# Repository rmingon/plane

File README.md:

# PLANE  with 3D models and specific hardware control system 

* SG90 servo
* LD-POWER motor 4300KV
* ESC 8A 
* 2-3s battery

### Thingiverse
[LINK](https://www.thingiverse.com/thing:6716661)

### 3d global view

## Hardware

* ESP32 wifi + bluetooth controller
* LORA 868mhz Long range communication with SMA connector
* 4 channels servos control
* XT30 battery connector
* MPU6050 giro and accel mcu
* BMP280 altimeter
* ESC connector

### 3d view

### Pcb view

### Schematic view

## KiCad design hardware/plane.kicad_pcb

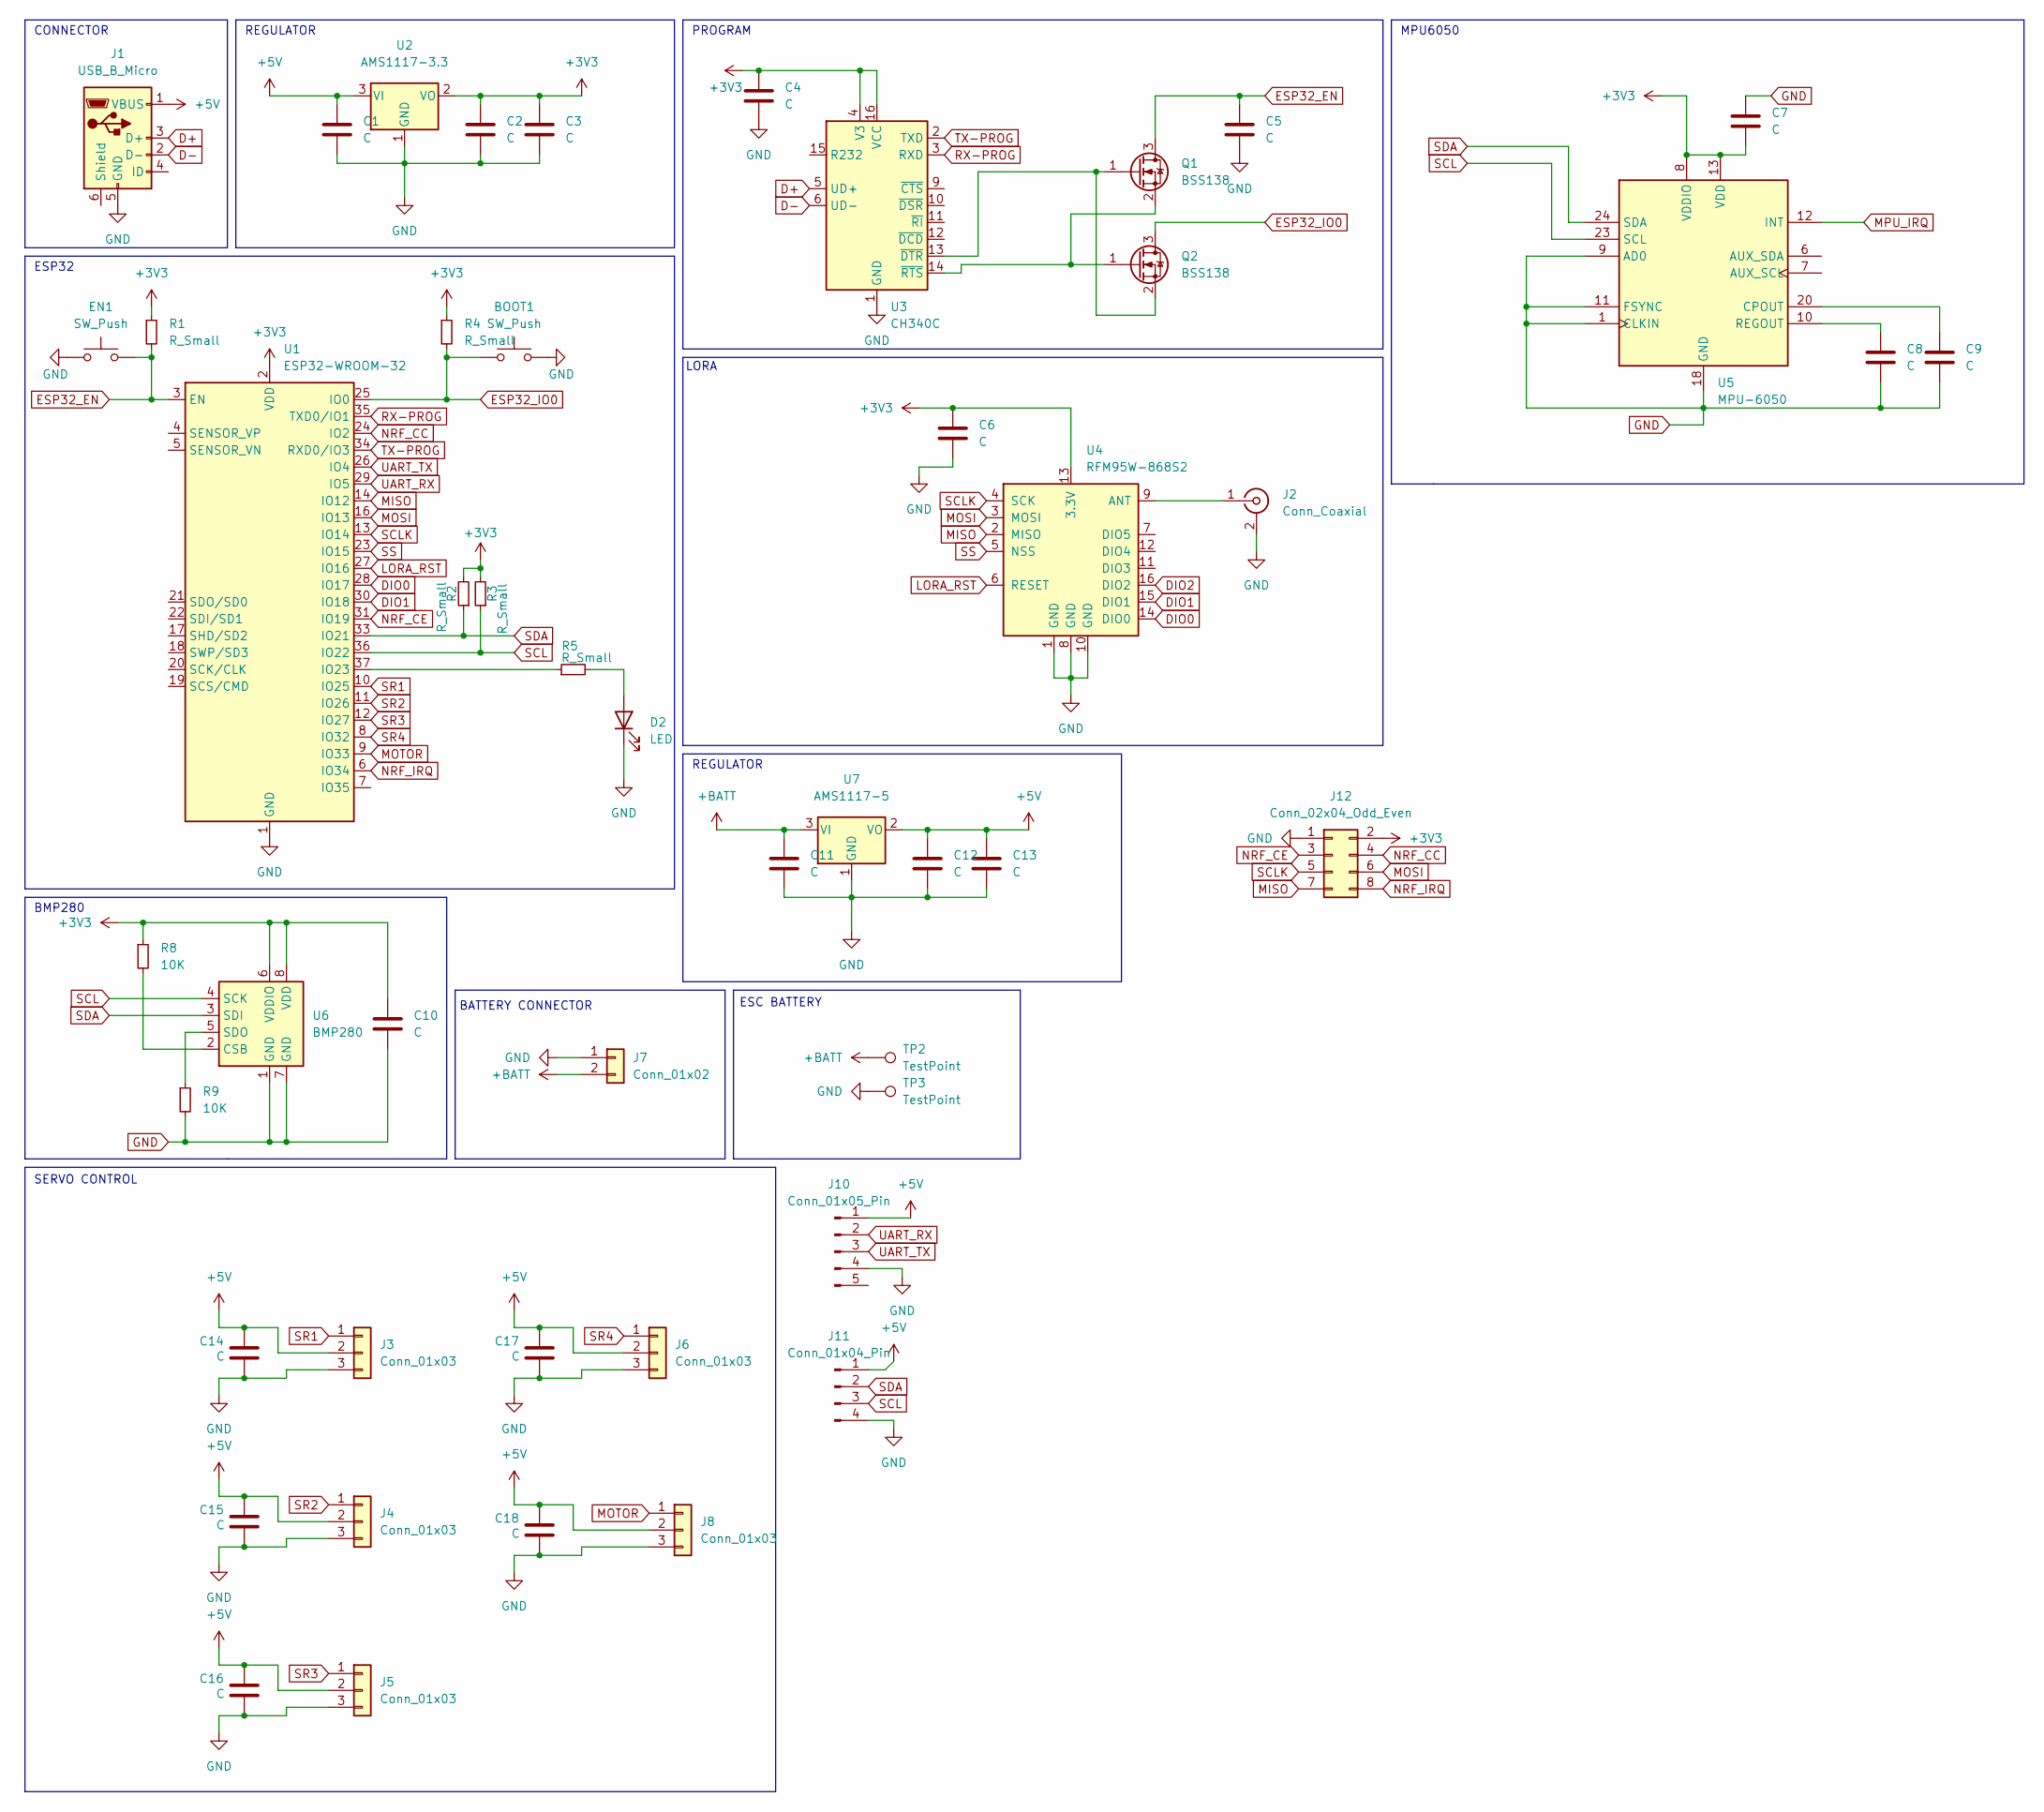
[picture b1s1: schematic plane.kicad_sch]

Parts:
BOOT1: SW_Push; SW_SPST_FSMSM
C1, C2, C3, C4, C5, C6, C7, C8, C9, C10, C11, C12, C13, C14, C15, C16, C17, C18: C; C_0603_1608Metric
D2: LED; LED_0603_1608Metric
EN1: SW_Push; SW_SPST_FSMSM
J1: USB_B_Micro; USB_Micro-B_Amphenol_10118194_Horizontal
J2: Conn_Coaxial; SMA_Samtec_SMA-J-P-H-ST-EM1_EdgeMount
J3, J4, J5, J6, J8: Conn_01x03; PinHeader_1x03_P2.54mm_Vertical
J7: Conn_01x02; AMASS_XT30U-F_1x02_P5.0mm_Vertical
J10: Conn_01x05_Pin; PinHeader_1x05_P2.54mm_Vertical
J11: Conn_01x04_Pin; PinHeader_1x04_P2.54mm_Vertical
J12: Conn_02x04_Odd_Even; PinHeader_2x04_P2.54mm_Vertical
Q1, Q2: BSS138; SOT-23
R1, R2, R3, R4, R5: R_Small; R_0603_1608Metric
R8, R9: 10K; R_0603_1608Metric
TP2, TP3: TestPoint; TestPoint_Pad_2.5x2.5mm
U1: ESP32-WROOM-32
U2: AMS1117-3.3; SOT-223-3_TabPin2
U3: CH340C; SOIC-16_3.9x9.9mm_P1.27mm
U4: RFM95W-868S2; HOPERF_RFM9XW_SMD
U5: MPU-6050; InvenSense_QFN-24_4x4mm_P0.5mm
U6: BMP280; Bosch_LGA-8_2x2.5mm_P0.65mm_ClockwisePinNumbering
U7: AMS1117-5; SOT-223-3_TabPin2

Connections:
+3V3: C2.1, C3.1, C4.1, C6.1, C7.2, C10.1, J12.2, R1.1, R2.2, R3.2, R4.1, R8.1, U1.2 (VDD), U2.2 (VO), U3.4 (V3), U3.16 (VCC), U4.13 (3.3V), U5.8 (VDDIO), U5.13 (VDD), U6.6 (VDDIO), U6.8 (VDD)
+5V: C1.1, C12.1, C13.1, C14.1, C15.1, C16.1, C17.1, C18.1, J1.1 (VBUS), J3.2, J4.2, J5.2, J6.2, J8.2, J10.1, J11.1, U2.3 (VI), U7.2 (VO)
+BATT: C11.1, J7.2, TP2.1, U7.3 (VI)
D+: J1.3 (D+), U3.5 (UD+)
D-: J1.2 (D-), U3.6 (UD-)
DIO0: U1.28 (IO17), U4.14 (DIO0)
DIO1: U1.30 (IO18), U4.15 (DIO1)
DIO2: U4.16 (DIO2)
ESP32_EN: C5.1, EN1.2, Q1.3 (D), R1.2, U1.3 (EN)
ESP32_IO0: BOOT1.1, Q2.3 (D), R4.2, U1.25 (IO0)
GND: BOOT1.2, C1.2, C2.2, C3.2, C4.2, C5.2, C6.2, C7.1, C8.2, C9.2, C10.2, C11.2, C12.2, C13.2, C14.2, C15.2, C16.2, C17.2, C18.2, D2.1 (K), EN1.1, J1.5 (GND), J2.2 (Ext), J3.3, J4.3, J5.3, J6.3, J7.1, J8.3, J10.4, J11.4, J12.1, R9.2, TP3.1, U1.1 (GND), U1.15 (GND), U1.38 (GND), U1.39 (GND), U2.1 (GND), U3.1 (GND), U4.1 (GND), U4.8 (GND), U4.10 (GND), U5.1 (CLKIN), U5.9 (AD0), U5.11 (FSYNC), U5.18 (GND), U6.1 (GND), U6.7 (GND), U7.1 (GND)
LORA_RST: U1.27 (IO16), U4.6 (RESET)
MISO: J12.7, U1.14 (IO12), U4.2 (MISO)
MOSI: J12.6, U1.16 (IO13), U4.3 (MOSI)
MOTOR: J8.1, U1.9 (IO33)
MPU_IRQ: U5.12 (INT)
NRF_CC: J12.4, U1.24 (IO2)
NRF_CE: J12.3, U1.31 (IO19)
NRF_IRQ: J12.8, U1.6 (IO34)
unnamed: D2.2 (A), R5.2
unnamed: J2.1 (In), U4.9 (ANT)
unnamed: Q1.1 (G), Q2.2 (S), U3.13 (~DTR)
unnamed: Q1.2 (S), Q2.1 (G), U3.14 (~RTS)
unnamed: R5.1, U1.37 (IO23)
unnamed: C9.1, U5.20 (CPOUT)
unnamed: C8.1, U5.10 (REGOUT)
unnamed: R8.2, U6.2 (CSB)
unnamed: R9.1, U6.5 (SDO)
RX-PROG: U1.35 (TXD0/IO1), U3.3 (RXD)
SCL: J11.3, R3.1, U1.36 (IO22), U5.23 (SCL), U6.4 (SCK)
SCLK: J12.5, U1.13 (IO14), U4.4 (SCK)
SDA: J11.2, R2.1, U1.33 (IO21), U5.24 (SDA), U6.3 (SDI)
SR1: J3.1, U1.10 (IO25)
SR2: J4.1, U1.11 (IO26)
SR3: J5.1, U1.12 (IO27)
SR4: J6.1, U1.8 (IO32)
SS: U1.23 (IO15), U4.5 (NSS)
TX-PROG: U1.34 (RXD0/IO3), U3.2 (TXD)
UART_RX: J10.2, U1.29 (IO5)
UART_TX: J10.3, U1.26 (IO4)

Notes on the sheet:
ESP32
REGULATOR
ESC BATTERY
PROGRAM
SERVO CONTROL
BMP280
BATTERY CONNECTOR
MPU6050
CONNECTOR
LORA

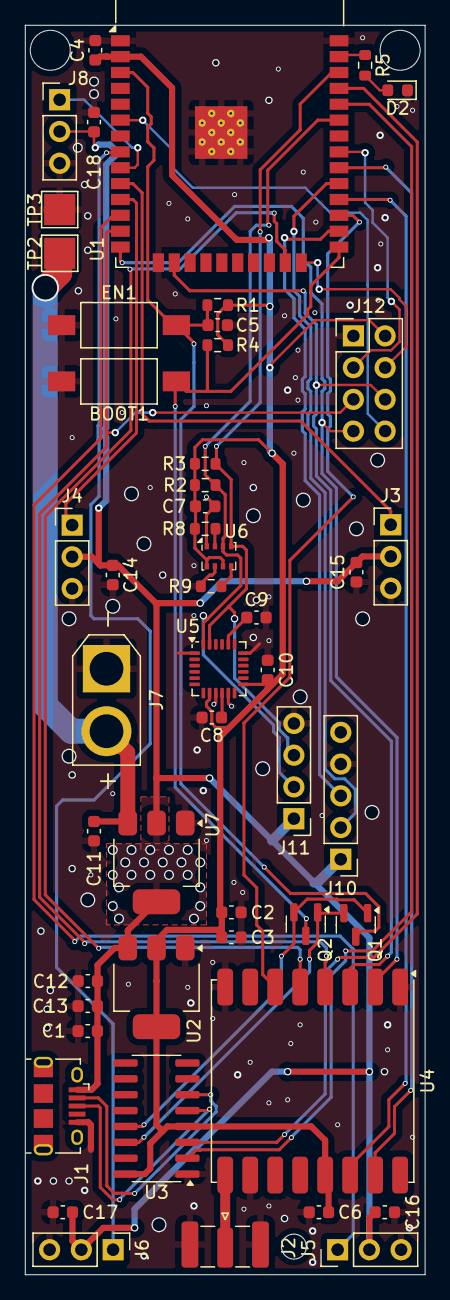
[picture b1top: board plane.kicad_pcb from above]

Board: 2 copper layers, 32.0 x 100.0 mm, 50 parts (0 on the bottom side), 38 nets.

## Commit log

2024-08-01 add readme +move views
2024-08-01 update motor kv
2024-08-02 add hardware
2024-08-02 add esp32 + program circuit
2024-08-02 update fuselage
2024-08-02 add lora
2024-08-02 add mpu + bmp
2024-08-02 add footprints
2024-08-02 add servos + pcb size
2024-08-02 add servo pin + wiring pcb
2024-08-02 wiring servo
2024-08-02 i2c wiring
2024-08-03 wiring + battery connector
2024-08-03 add views
2024-08-03 add hardware info
2024-08-03 pcb battery connector
2024-08-03 add sma connector info
2024-08-03 add esc connector
2024-08-03 esc connector
2024-08-05 update 3d
2024-08-05 update setting
2024-08-14 add code
2024-08-14 add mpu6050
2024-08-24 upgrade esc connector & sma
2024-08-24 rewire
2025-01-05 update flaps
2025-01-07 remove waiting
2025-01-17 add esc calibrate + pid setting
2025-01-17 add roll + yaw method
2025-01-21 add controller code
2025-01-21 add minimal config + code nunchuck
2025-01-21 plane with extended wings
2025-01-21 add udp server + access point mode
2025-01-21 add nunchuck udp parsing
2025-01-21 parse data in nunchuck json
2025-01-22 add servo connector
2025-01-23 add esc control via nunchuk
2025-02-24 add i2c and uart connectors
2025-04-06 add gps lib
2025-04-06 add gps reading
2025-04-07 add minimal front angular
2025-04-08 add mininal rxjs ws client
2025-04-08 cindt je t"aime z t lz qioq d
2025-04-11 add hmc lib + send data over lora
2025-04-11 add front plane instruments
2025-04-24 update PID and data lora
2025-07-20 add nrf24l01 connector
